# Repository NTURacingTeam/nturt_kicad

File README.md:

# NTU Racing Team KiCad Files

## Guide for configuring path variables and libraries

> [!NOTE]
> Before you start, please include the appropriate libraries and path variables to ensure components and their resources can be loaded correctly!

### 1. Configuring path variable

\

### 2. Configuring libraries
> [!NOTE]
> Configure symbol libraries and footprint libraries according to the README files located in each generation's directory. Images shown here are only for demonstration purposes only.

## Adding 3D models

1. Copy the .step/.wrl files to `EPx/Libraries/3d_models` folder
2. In the footprint editor (press Ctrl+E on a footprint in the PCB editor), open footprint properties, navigate to the 3D Models tab, and select the 3D model file with the folder icon to the left of the Show checkbox.
3. The path should be replaced with `${NTURT_KICAD_ROOT}/EPx/Libraries/3d_models/...`, if not, then you will need to set up the path variable.
4. Adjust the position of the model.
> [!NOTE]
> For a part that a 3D model would be helpful, if it is a part that came with KiCad, then consider "Save as" in the footprint editor to the project library, then edit the 3D model.\
> If it is already from a project library, remember to select "Open in library XXX" if it says "Editing XXX from board." on top. After you're done, right click the footprint in the PCB editor and select Update Footprint, check Update/reset 3D models.

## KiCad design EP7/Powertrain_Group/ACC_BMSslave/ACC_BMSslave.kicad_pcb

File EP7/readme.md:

# Libraries

## Path variable
Add `NTURT_KICAD_ROOT` to PATH environment variable, pointing to the git root of this repository.

## Symbols
Add the following symbol libraries with nickname:
  - `nturt_kicad_lib_EP7`:
```
${NTURT_KICAD_ROOT}/EP7/Libraries/nturt_kicad_lib_EP7.kicad_sym
```

## Footprints
Add the following footprint libraries with nickname:
  - `nturt_kicad_lib_EP7`:
```
${NTURT_KICAD_ROOT}/EP7/Libraries/nturt_kicad_lib_EP7.pretty
```

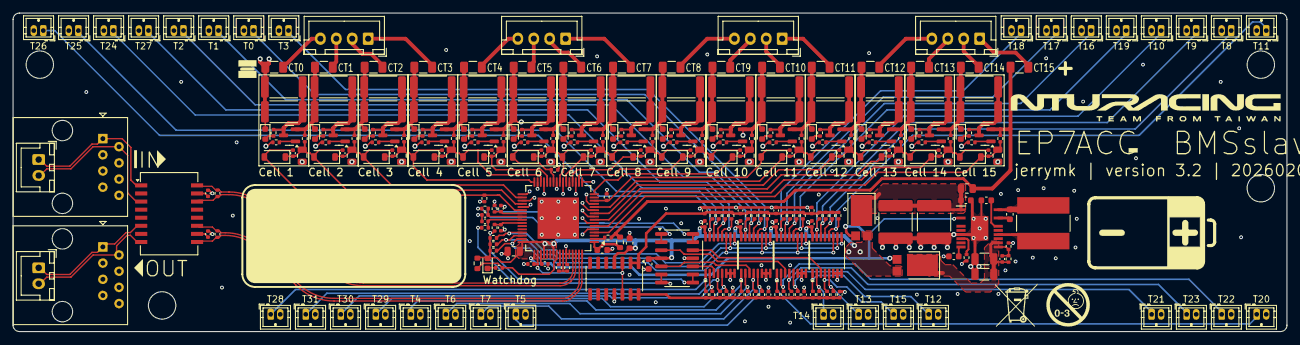
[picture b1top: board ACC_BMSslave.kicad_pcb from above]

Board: 4 copper layers, 200.0 x 50.0 mm, 310 parts (0 on the bottom side), 188 nets.

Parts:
C1, C2, C15: 100n; C_0603_1608Metric
C3, C57: 1u; C_0603_1608Metric
C4, C5, C6, C7: 10n; C_0402_1005Metric
C8, C9: 1u; C_0402_1005Metric
C10, C11: 100p; C_0402_1005Metric
C12: 1u; C_0805_2012Metric
C13, C63: 2.2u; C_2220_5750Metric
C14: 100p; C_0603_1608Metric
C16: 4.7p; C_0402_1005Metric
C17: 2.2u; C_0603_1608Metric
C18, C62: 22u; C_1206_3216Metric
C19, C20, C21, C22, C23, C24, C25, C26, C28, C30, C32, C34, C36, C38, C40, C42, C44, C46, C48, C50, C52, C54, C56, C58, C59, C60, C61: 100n; C_0402_1005Metric
C27, C29, C31, C33, C35, C37, C39, C41, C43, C45, C47, C49, C51, C53, C55: 100n 100V; C_0805_2012Metric
D1: BLUE; LED_0603_1608Metric
D2, D3, D4, D5, D6, D7, D8, D9, D10, D11, D12, D13, D14, D15, D16: RED; LED_0603_1608Metric
F1, F2, F3, F4, F5, F6, F7, F8, F9, F10, F11, F12, F13, F14, F15, F16: 0466.250NR; Fuse_1206_3216Metric
H1, H2, H3, H4: MountingHole; MountingHole_4.3mm_M4_ISO14580
IC1: ADBMS1818ASWAZ-R7; LQFP-64-1EP_10x10mm_P0.5mm_EP6.5x6.5mm
IC2: LT8631IFE#PBF; TSSOP-20 FE20(16) (EP Variation CB)
IC3, IC4, IC5, IC6, IC7, IC8, IC9, IC10, IC11, IC12, IC13, IC14, IC15, IC16, IC17: NX2301P,215; SOT-23
J1, J2, J3, J4: JST XH; JST_XH_B4B-XH-A_1x04_P2.50mm_Vertical
J5, J6, J7, J8, J9, J10, J11, J12, J13, J14, J15, J16, J17, J18, J19, J20, J21, J22, J23, J24, J25, J26, J27, J28, J29, J30, J31, J32, J33, J34, J35, J36: JST ZH; JST_ZH_B2B-ZR_1x02_P1.50mm_Vertical
J37, J38: RJ45; RJ45_Amphenol_54602-x08_Horizontal
J39: isoSPI_out; JST_XH_B2B-XH-A_1x02_P2.50mm_Vertical
J40: isoSPI_in; JST_XH_B2B-XH-A_1x02_P2.50mm_Vertical
L1: 22u/2A; L_Bourns-SRN8040_8x8.15mm
Q1, Q2: Q_NPN; D_PowerDI-5
R1: 100R; R_0805_2012Metric
R2: 100R; R_0603_1608Metric
R3, R4, R5, R6, R60, R65, R70, R75, R80, R85, R90, R95, R96, R101, R122, R123, R124, R125, R126: 10R; R_0402_1005Metric
R7, R8, R9, R10, R15, R16: 100R; R_0402_1005Metric
R11, R12, R13, R52, R56, R61, R66, R71, R76, R81, R86, R91, R97, R102, R106, R110, R114, R118: 1k; R_0402_1005Metric
R14: 1M; R_0603_1608Metric
R17: 24k; R_0402_1005Metric
R18: 1M/1%; R_0402_1005Metric
R19: 127k/1%; R_0402_1005Metric
R20, R21, R22, R23, R24, R25, R26, R27, R28, R29, R30, R31, R32, R33, R34, R35, R36, R37, R38, R39, R40, R41, R42, R43, R44, R45, R46, R47, R48, R49, R50, R51: 10k; R_0402_1005Metric
R53, R54, R57, R58, R62, R63, R67, R68, R72, R73, R77, R78, R82, R83, R87, R88, R92, R93, R98, R99, R103, R104, R107, R108, R111, R112, R115, R116, R119, R120: 51R; R_2512_6332Metric
R55, R59, R64, R69, R74, R79, R84, R89, R94, R100, R105, R109, R113, R117, R121: 3.3k; R_0402_1005Metric
R127, R128, R129: 47k; R_0402_1005Metric
TR1: Wuerth_749013011A; Transformer_Ethernet_Wuerth_749013011A
U1, U6: LM324DT; SO-14_3.9x8.65mm_P1.27mm
U2, U3, U4, U5: CD4051B; TSSOP-16_4.4x5mm_P0.65mm
Z1, Z2, Z3, Z4, Z5, Z6, Z7, Z8, Z9, Z10, Z11, Z12, Z13, Z14, Z15: MMSZ4692T1G; D_SOD-123

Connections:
/C0: C42.2, IC1.38 (C0), R6.2, Z8.2 (A)
/C1: C28.2, C41.1, C42.1, IC1.36 (C1), R95.2, Z1.2 (A), Z8.1 (K)
/C2: C27.1, C28.1, C30.2, IC1.34 (C2), R60.2, Z1.1 (K), Z2.2 (A)
/C3: C29.1, C30.1, C32.2, IC1.32 (C3), R65.2, Z2.1 (K), Z3.2 (A)
/C4: C31.1, C32.1, C34.2, IC1.30 (C4), R70.2, Z3.1 (K), Z4.2 (A)
/C5: C33.1, C34.1, IC1.28 (C5), R75.2, Z4.1 (K)
/C6: C36.2, IC1.26 (C6), R5.2, Z5.2 (A)
/C7: C35.1, C36.1, C38.2, IC1.24 (C7), R80.2, Z5.1 (K), Z6.2 (A)
/C8: C37.1, C38.1, C40.2, IC1.22 (C8), R85.2, Z6.1 (K), Z7.2 (A)
/C9: C39.1, C40.1, C44.2, IC1.20 (C9), R90.2, Z7.1 (K), Z9.2 (A)
/C10: C43.1, C44.1, C46.2, IC1.18 (C10), R96.2, Z9.1 (K), Z10.2 (A)
/C11: C45.1, C46.1, IC1.16 (C11), R101.2, Z10.1 (K)
/C12: C48.2, IC1.14 (C12), R4.2, Z11.2 (A)
/C13: C47.1, C48.1, C50.2, IC1.12 (C13), R122.2, Z11.1 (K), Z12.2 (A)
/C14: C49.1, C50.1, C52.2, IC1.10 (C14), R123.2, Z12.1 (K), Z13.2 (A)
/C15: C51.1, C52.1, C54.2, IC1.8 (C15), R124.2, Z13.1 (K), Z14.2 (A)
/C16: C53.1, C54.1, C56.2, IC1.6 (C16), R125.2, Z14.1 (K), Z15.2 (A)
/C17: C55.1, C56.1, IC1.4 (C17), R126.2, Z15.1 (K)
/C18: IC1.2 (C18), R3.2
/CT1: D2.1 (K), F2.2, IC4.2 (S), R53.1, R54.1, R95.1
/CT2: D4.1 (K), F3.2, IC3.2 (S), R60.1, R62.1, R63.1
/CT3: D5.1 (K), F4.2, IC5.2 (S), R65.1, R67.1, R68.1
/CT4: D6.1 (K), F5.2, IC6.2 (S), R70.1, R72.1, R73.1
/CT5: D7.1 (K), F6.2, IC7.2 (S), R5.1, R75.1, R77.1, R78.1
/CT6: D8.1 (K), F7.2, IC8.2 (S), R80.1, R82.1, R83.1
/CT7: D9.1 (K), F8.2, IC9.2 (S), R85.1, R87.1, R88.1
/CT8: D10.1 (K), F9.2, IC10.2 (S), R90.1, R92.1, R93.1
/CT9: D11.1 (K), F10.2, IC11.2 (S), R96.1, R98.1, R99.1
/CT10: D12.1 (K), F11.2, IC12.2 (S), R4.1, R101.1, R103.1, R104.1
/CT11: D13.1 (K), F12.2, IC13.2 (S), R107.1, R108.1, R122.1
/CT12: D14.1 (K), F13.2, IC14.2 (S), R111.1, R112.1, R123.1
/CT13: D15.1 (K), F14.2, IC15.2 (S), R115.1, R116.1, R124.1
/CT14: D16.1 (K), F15.2, IC16.2 (S), R119.1, R120.1, R125.1
/CT15: F16.2, IC17.2 (S), R1.1, R2.1, R3.1, R126.1
/DRIVE: IC1.49 (DRIVE), IC2.3 (EN/UV), Q1.B, Q2.B
/GPIO1: C4.1, IC1.39 (GPIO1), R7.2
/GPIO2: C5.1, IC1.40 (GPIO2), R8.2
/GPIO3: C7.1, IC1.41 (GPIO3), R10.2
/GPIO4: C6.1, IC1.42 (GPIO4), R9.2
/GPIO7: IC1.45 (GPIO7), R129.1, U2.9 (C), U3.9 (C), U4.9 (C), U5.9 (C)
/GPIO8: IC1.46 (GPIO8), R128.1, U2.10 (B), U3.10 (B), U4.10 (B), U5.10 (B)
/GPIO9: IC1.47 (GPIO9), R127.1, U2.11 (A), U3.11 (A), U4.11 (A), U5.11 (A)
/IN_N: IC1.61 (CSB), R16.1, TR1.16 (TX+)
/IN_P: IC1.62 (SCK), R16.2, TR1.14 (TX-)
/ISOSPI_IN+: J38.2, J40.2, TR1.3 (TD-)
/ISOSPI_IN-: J38.1, J40.1, TR1.1 (TD+)
/ISOSPI_OUT+: J37.2, J39.2, TR1.8 (RD-)
/ISOSPI_OUT-: J37.1, J39.1, TR1.6 (RD+)
/OUT_N: IC1.63 (IMB), R15.1, TR1.11 (RX+)
/OUT_P: IC1.64 (IPB), R15.2, TR1.9 (RX-)
/S1: IC1.37 (S1), R59.1
/S2: IC1.35 (S2), R55.1
/S3: IC1.33 (S3), R64.1
/S4: IC1.31 (S4), R69.1
/S5: IC1.29 (S5), R74.1
/S7: IC1.25 (S7), R79.1
/S8: IC1.23 (S8), R84.1
/S9: IC1.21 (S9), R89.1
/S10: IC1.19 (S10), R94.1
/S11: IC1.17 (S11), R100.1
/S13: IC1.13 (S13), R105.1
/S14: IC1.11 (S14), R109.1
/S15: IC1.9 (S15), R113.1
/S16: IC1.7 (S16), R117.1
/S17: IC1.5 (S17), R121.1
/T0: J5.1, R28.1, U3.13 (X0)
/T1: J13.1, R29.1, U3.14 (X1)
/T2: J21.1, R30.1, U3.15 (X2)
/T3: J29.1, R31.1, U3.12 (X3)
/T4: J6.1, R32.1, U3.1 (X4)
/T5: J14.1, R33.1, U3.5 (X5)
/T6: J22.1, R34.1, U3.2 (X6)
/T7: J30.1, R35.1, U3.4 (X7)
/T8: J7.1, R44.1, U5.13 (X0)
/T9: J15.1, R45.1, U5.14 (X1)
/T10: J23.1, R46.1, U5.15 (X2)
/T11: J31.1, R47.1, U5.12 (X3)
/T12: J8.1, R48.1, U5.1 (X4)
/T13: J16.1, R49.1, U5.5 (X5)
/T14: J24.1, R50.1, U5.2 (X6)
/T15: J32.1, R51.1, U5.4 (X7)
/T16: J9.1, R36.1, U4.13 (X0)
/T17: J17.1, R37.1, U4.14 (X1)
/T18: J25.1, R38.1, U4.15 (X2)
/T19: J33.1, R39.1, U4.12 (X3)
/T20: J10.1, R40.1, U4.1 (X4)
/T21: J18.1, R41.1, U4.5 (X5)
/T22: J26.1, R42.1, U4.2 (X6)
/T23: J34.1, R43.1, U4.4 (X7)
/T24: J11.1, R20.1, U2.13 (X0)
/T25: J19.1, R21.1, U2.14 (X1)
/T26: J27.1, R22.1, U2.15 (X2)
/T27: J35.1, R23.1, U2.12 (X3)
/T28: J12.1, R24.1, U2.1 (X4)
/T29: J20.1, R25.1, U2.5 (X5)
/T30: J28.1, R26.1, U2.2 (X6)
/T31: J36.1, R27.1, U2.4 (X7)
/VP: C2.1, IC1.1 (V+), R2.2
/VREF2: C9.1, IC1.50 (VREF2), U6.3 (+), U6.12 (+)
/power/VIN: C1.1, C13.1, C63.1, IC2.1 (VIN), Q2.C, R1.2
/tprobe_mux1/OUT: U1.10 (+), U2.3 (X)
/tprobe_mux1/VREF: C20.1, C22.1, C24.1, C26.1, R20.2, R21.2, R22.2, R23.2, R28.2, R29.2, R30.2, R31.2, R36.2, R37.2, R38.2, R39.2, R44.2, R45.2, R46.2, R47.2, U6.1, U6.2 (-)
/tprobe_mux1/VREF_b: C58.1, C59.1, C60.1, C61.1, R24.2, R25.2, R26.2, R27.2, R32.2, R33.2, R34.2, R35.2, R40.2, R41.2, R42.2, R43.2, R48.2, R49.2, R50.2, R51.2, U6.13 (-), U6.14
/tprobe_mux2/OUT: U1.5 (+), U3.3 (X)
/tprobe_mux3/OUT: U1.3 (+), U4.3 (X)
/tprobe_mux4/OUT: U1.12 (+), U5.3 (X)
Earth: C1.2, C2.2, C3.2, C4.2, C5.2, C6.2, C7.2, C8.2, C9.2, C10.2, C11.2, C12.2, C13.2, C14.2, C17.2, C18.2, C19.2, C20.2, C21.2, C22.2, C23.2, C24.2, C25.2, C26.2, C27.2, C29.2, C31.2, C33.2, C35.2, C37.2, C39.2, C41.2, C43.2, C45.2, C47.2, C49.2, C51.2, C53.2, C55.2, C57.2, C58.2, C59.2, C60.2, C61.2, C62.2, C63.2, D3.1 (K), F1.2, IC1.59 (V-_1), IC1.60 (V-_2), IC1.65 (V-_3), IC2.7 (SYNC/MODE), IC2.21 (GND), J5.2, J6.2, J7.2, J8.2, J9.2, J10.2, J11.2, J12.2, J13.2, J14.2, J15.2, J16.2, J17.2, J18.2, J19.2, J20.2, J21.2, J22.2, J23.2, J24.2, J25.2, J26.2, J27.2, J28.2, J29.2, J30.2, J31.2, J32.2, J33.2, J34.2, J35.2, J36.2, R6.1, R11.2, R17.2, R19.2, R57.1, R58.1, U1.11 (V-), U2.6 (INH), U2.7 (VEE), U2.8 (VSS), U3.6 (INH), U3.7 (VEE), U3.8 (VSS), U4.6 (INH), U4.7 (VEE), U4.8 (VSS), U5.6 (INH), U5.7 (VEE), U5.8 (VSS), U6.11 (V-)
unnamed: D1.1 (K), R13.1
unnamed: D2.2 (A), R52.2
unnamed: D3.2 (A), R56.2
unnamed: D4.2 (A), R61.2
unnamed: D5.2 (A), R66.2
unnamed: D6.2 (A), R71.2
unnamed: D7.2 (A), R76.2
unnamed: D8.2 (A), R81.2
unnamed: D9.2 (A), R86.2
unnamed: D10.2 (A), R91.2
unnamed: D11.2 (A), R97.2
unnamed: D12.2 (A), R102.2
unnamed: D13.2 (A), R106.2
unnamed: D14.2 (A), R110.2
unnamed: D15.2 (A), R114.2
unnamed: D16.2 (A), R118.2
unnamed: IC1.57 (IBIAS), R12.1
unnamed: IC1.58 (ICMP), R11.1, R12.2
unnamed: C8.1, IC1.51 (VREF1)
unnamed: IC1.56 (WDT), R13.2, R14.2
unnamed: C15.1, IC2.18 (BST)
unnamed: C16.1, IC2.11 (FB), R18.2, R19.1
unnamed: IC2.14 (IND), L1.1
unnamed: C17.1, IC2.16 (INTVCC)
unnamed: IC2.8 (RT), R17.1
unnamed: C15.2, IC2.20 (SW), L1.2
unnamed: C14.1, IC2.10 (TR/SS)
unnamed: C16.2, C18.1, C62.1, IC2.12 (VOUT), Q1.C, R18.1
unnamed: IC3.3 (D), R52.1, R53.2, R54.2
unnamed: IC3.1 (G), R55.2
unnamed: IC4.3 (D), R56.1, R57.2, R58.2
unnamed: IC4.1 (G), R59.2
unnamed: IC5.3 (D), R61.1, R62.2, R63.2
unnamed: IC5.1 (G), R64.2
unnamed: IC6.3 (D), R66.1, R67.2, R68.2
unnamed: IC6.1 (G), R69.2
unnamed: IC7.3 (D), R71.1, R72.2, R73.2
unnamed: IC7.1 (G), R74.2
unnamed: IC8.3 (D), R76.1, R77.2, R78.2
unnamed: IC8.1 (G), R79.2
unnamed: IC9.3 (D), R81.1, R82.2, R83.2
unnamed: IC9.1 (G), R84.2
unnamed: IC10.3 (D), R86.1, R87.2, R88.2
unnamed: IC10.1 (G), R89.2
unnamed: IC11.3 (D), R91.1, R92.2, R93.2
unnamed: IC11.1 (G), R94.2
unnamed: IC12.3 (D), R97.1, R98.2, R99.2
unnamed: IC12.1 (G), R100.2
unnamed: IC13.3 (D), R102.1, R103.2, R104.2
unnamed: IC13.1 (G), R105.2
unnamed: IC14.3 (D), R106.1, R107.2, R108.2
unnamed: IC14.1 (G), R109.2
unnamed: IC15.3 (D), R110.1, R111.2, R112.2
unnamed: IC15.1 (G), R113.2
unnamed: IC16.3 (D), R114.1, R115.2, R116.2
unnamed: IC16.1 (G), R117.2
unnamed: IC17.3 (D), R118.1, R119.2, R120.2
unnamed: IC17.1 (G), R121.2
unnamed: F4.1, J1.1
unnamed: F3.1, J1.2
unnamed: F2.1, J1.3
unnamed: F1.1, J1.4
unnamed: F8.1, J2.1
unnamed: F7.1, J2.2
unnamed: F6.1, J2.3
unnamed: F5.1, J2.4
unnamed: F12.1, J3.1
unnamed: F11.1, J3.2
unnamed: F10.1, J3.3
unnamed: F9.1, J3.4
unnamed: F16.1, J4.1
unnamed: F15.1, J4.2
unnamed: F14.1, J4.3
unnamed: F13.1, J4.4
unnamed: C10.1, TR1.10 (C_RX)
unnamed: C11.1, TR1.15 (C_TX)
unnamed: R8.1, U1.1, U1.2 (-)
unnamed: R10.1, U1.6 (-), U1.7
unnamed: R9.1, U1.8, U1.9 (-)
unnamed: R7.1, U1.13 (-), U1.14
VREG: C3.1, C12.1, C19.1, C21.1, C23.1, C25.1, C57.1, D1.2 (A), IC1.48 (VREG), IC1.52 (DTEN), IC1.55 (ISOMD), Q1.E, Q2.E, R14.1, R127.2, R128.2, R129.2, U1.4 (V+), U2.16 (VDD), U3.16 (VDD), U4.16 (VDD), U5.16 (VDD), U6.4 (V+)

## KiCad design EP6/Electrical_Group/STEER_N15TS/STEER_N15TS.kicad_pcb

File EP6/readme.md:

# Libraries

## Path variable
Add `NTURT_KICAD_ROOT` to PATH environment variable, pointing to the git root of this repository.

## Symbols
Add the following symbol libraries with nickname:
  - `nturt_kicad_lib_EP6`:
```
${NTURT_KICAD_ROOT}/EP6/Project_Library_EP6/nturt_kicad_lib.kicad_sym
```
  - `SamacSys_Parts_EP6`:
```
${NTURT_KICAD_ROOT}/EP6/Project_Library_EP6/SamacSys_Parts.kicad_sym
```

## Footprints
Add the following footprint libraries with nickname:
  - `nturt_kicad_lib_EP6`:
```
${NTURT_KICAD_ROOT}/EP6/Project_Library_EP6/nturt_kicad_lib.pretty
```
  - `SamacSys_Parts_EP6`:
```
${NTURT_KICAD_ROOT}/EP6/Project_Library_EP6/SamacSys_Parts.pretty
```

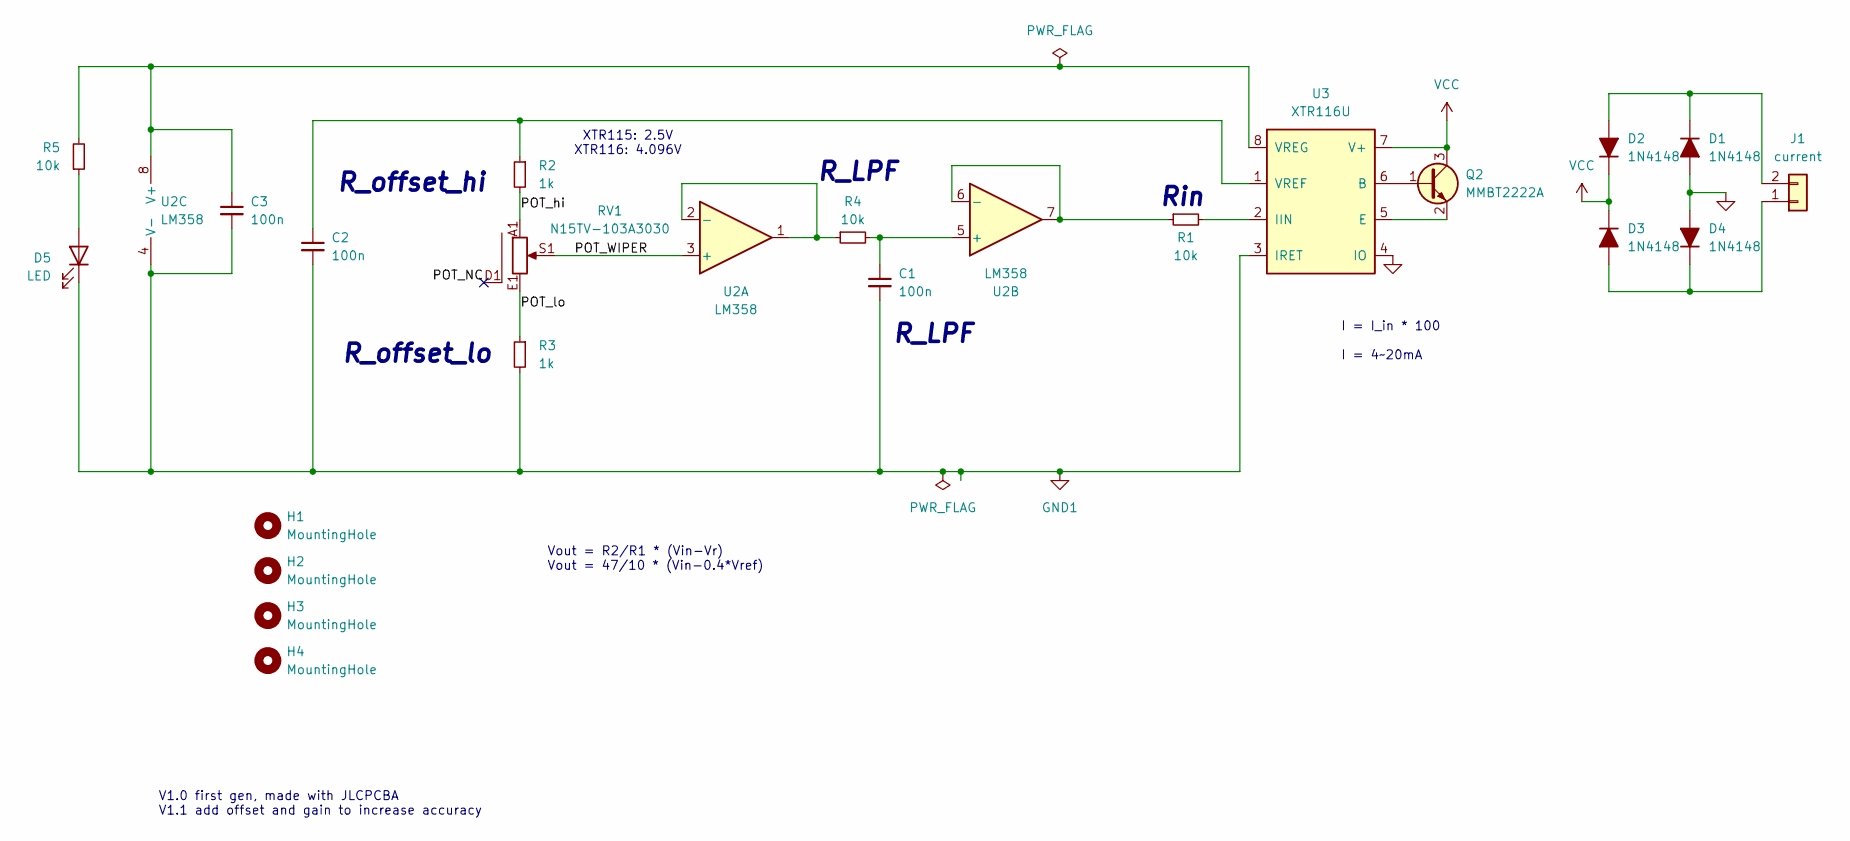
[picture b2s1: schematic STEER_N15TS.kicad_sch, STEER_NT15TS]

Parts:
C1, C2, C3: 100n; C_0603_1608Metric
D1, D2, D3, D4: 1N4148; D_SOD-323_HandSoldering
D5: LED; LED_0603_1608Metric
H1, H2, H3, H4: MountingHole; MountingHole_3.2mm_M3
J1: current; JST_XH_S2B-XH-A_1x02_P2.50mm_Horizontal; Part Number 1-0201FBV0T
Q2: MMBT2222A; SOT-23
R1, R4, R5: 10k; R_0603_1608Metric
R2, R3: 1k; R_0603_1608Metric
RV1: N15TV-103A3030; N15TS103A3030
U2: LM358; SOIC-8_3.9x4.9mm_P1.27mm
U3: XTR116U; SOIC-8_3.9x4.9mm_P1.27mm

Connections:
/POT_NC: RV1.D1 (DUMMY)
/POT_WIPER: RV1.S1 (WIPER), U2.3 (+)
/POT_hi: R2.2, RV1.A1 (INITIAL)
/POT_lo: R3.1, RV1.E1 (FINAL)
GND: D1.2 (A), D4.2 (A), U3.4 (IO)
GND1: C1.2, C2.2, C3.2, D5.1 (K), R3.2, U2.4 (V-), U3.3 (IRET)
unnamed: D1.1 (K), D2.2 (A), J1.2
unnamed: D3.2 (A), D4.1 (K), J1.1
unnamed: D5.2 (A), R5.1
unnamed: Q2.1 (B), U3.6 (B)
unnamed: Q2.2 (E), U3.5 (E)
unnamed: R4.1, U2.1, U2.2 (-)
unnamed: C1.1, R4.2, U2.5 (+)
unnamed: R1.1, U2.6 (-), U2.7
unnamed: C3.1, R5.2, U2.8 (V+), U3.8 (VREG)
unnamed: R1.2, U3.2 (IIN)
unnamed: C2.1, R2.1, U3.1 (VREF)
VCC: D2.1 (K), D3.1 (K), Q2.3 (C), U3.7 (V+)

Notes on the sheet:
R_offset_lo
Vout = R2/R1 * (Vin-Vr) Vout = 47/10 * (Vin-0.4*Vref)
R_offset_hi
I = I_in * 100 I = 4~20mA
R_LPF
XTR115: 2.5V XTR116: 4.096V
V1.0 first gen, made with JLCPCBA V1.1 add offset and gain to increase accuracy
Rin

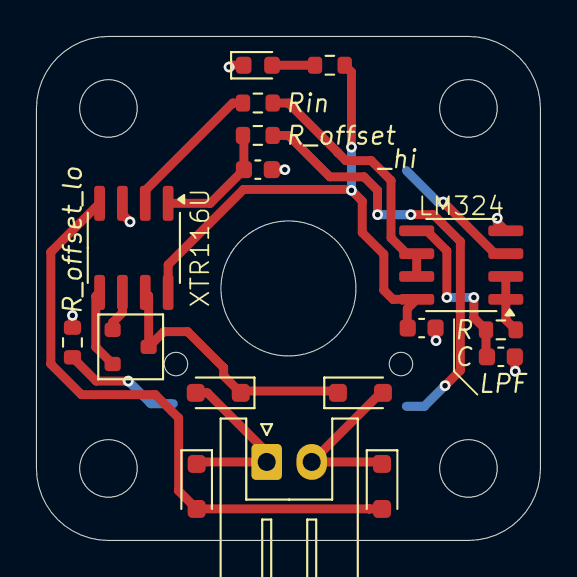
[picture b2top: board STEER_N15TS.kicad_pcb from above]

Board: 2 copper layers, 28.0 x 28.0 mm, 22 parts (1 on the bottom side), 17 nets.

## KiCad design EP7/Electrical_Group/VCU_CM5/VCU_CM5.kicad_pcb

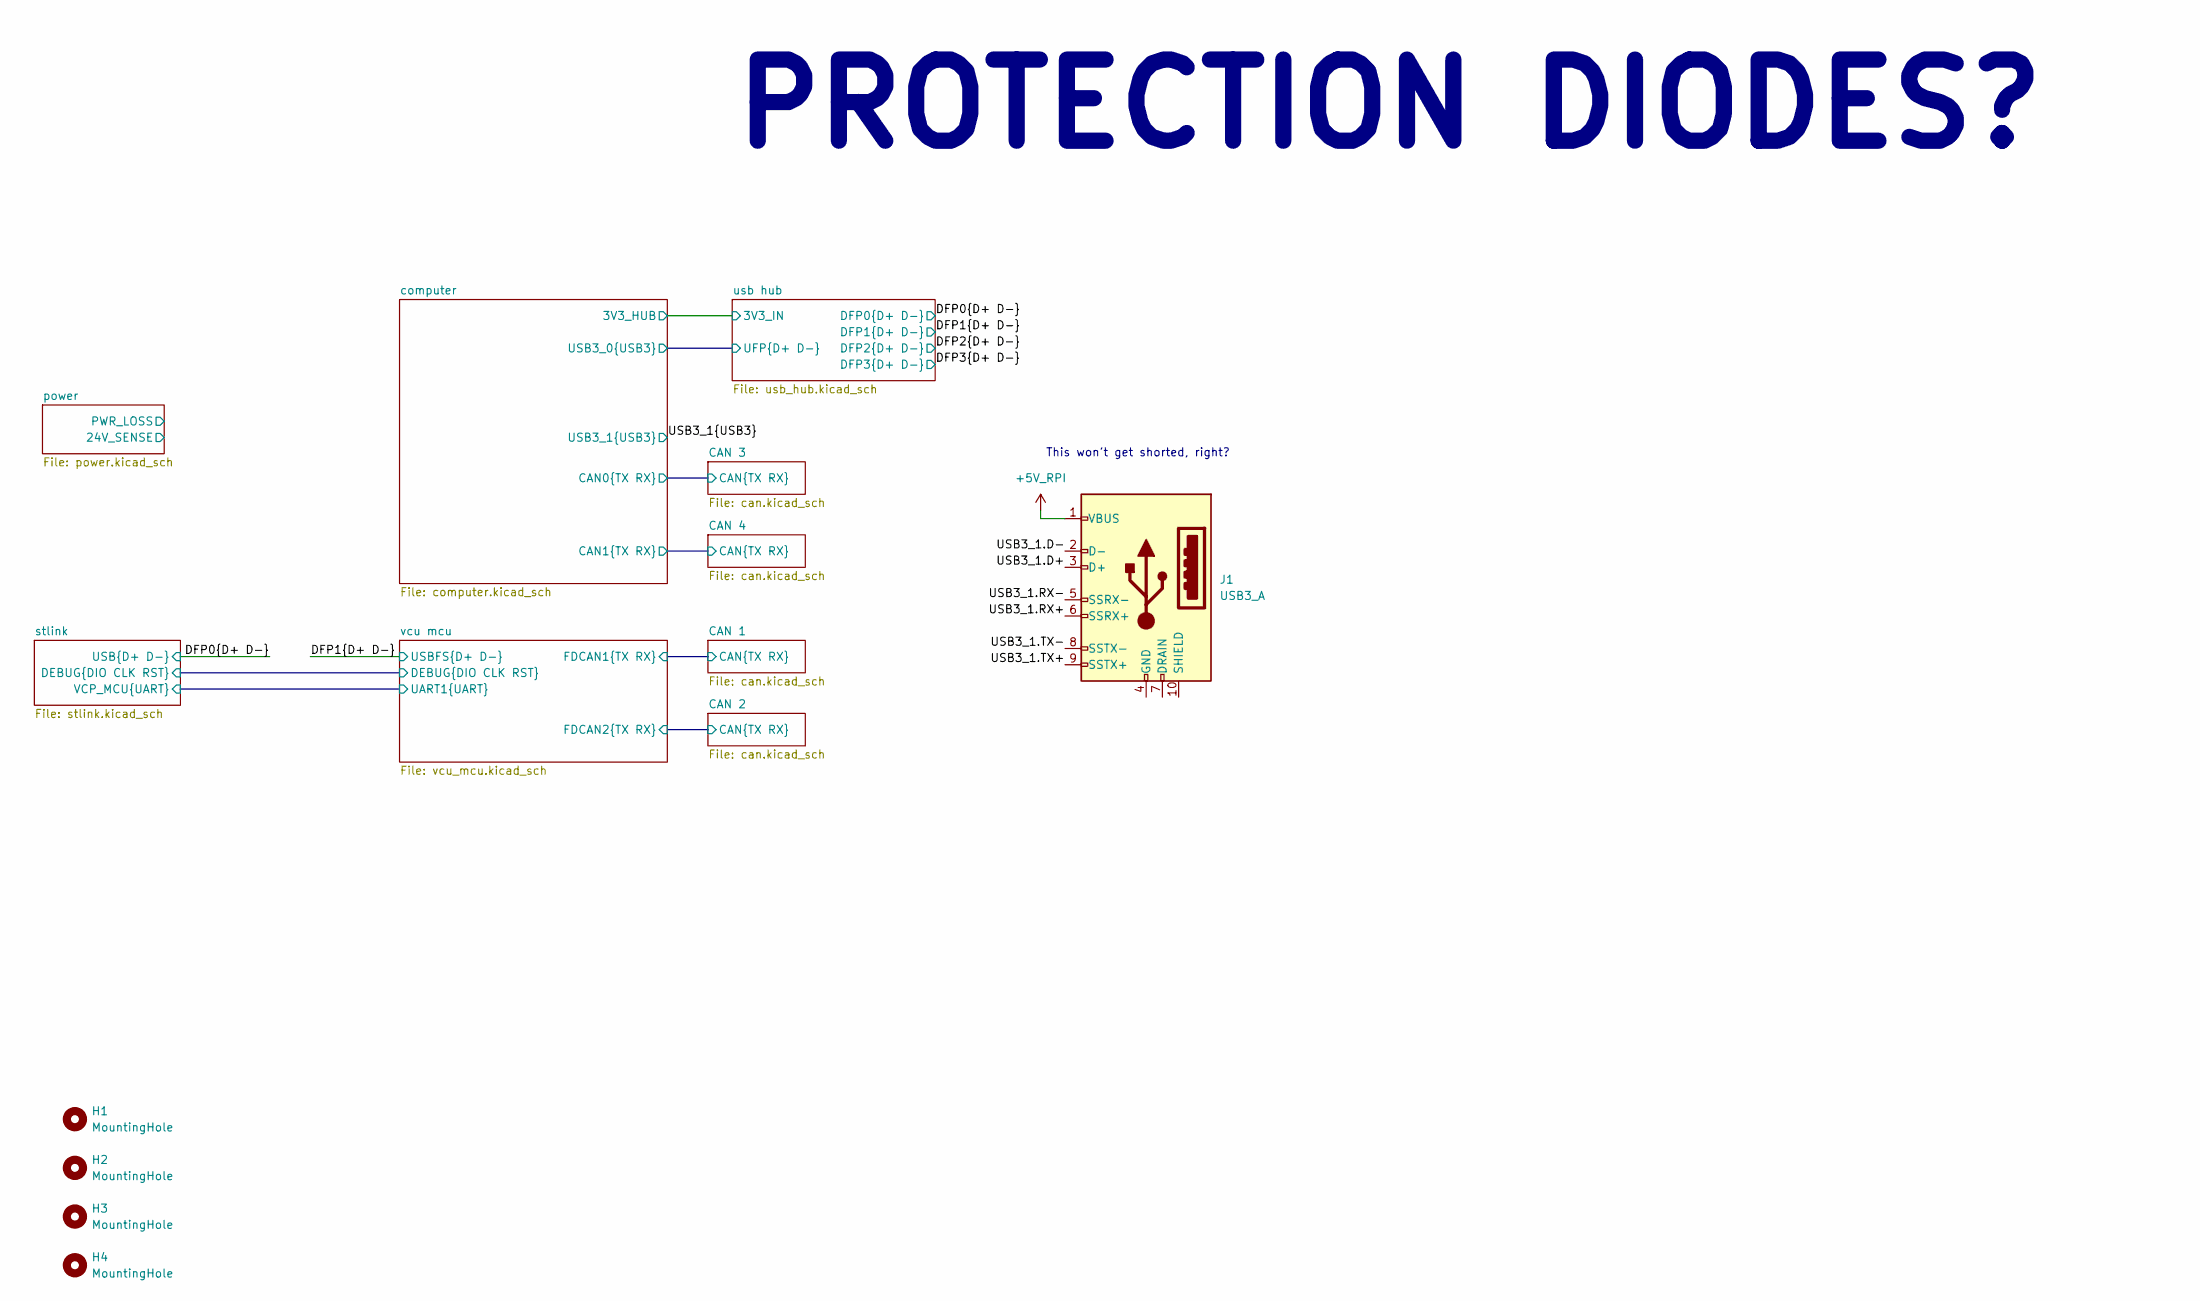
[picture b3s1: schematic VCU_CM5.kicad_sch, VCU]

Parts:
H1, H2, H3, H4: MountingHole; MountingHole_3.2mm_M3
J1: USB3_A; USB3_A_Molex_48393-001

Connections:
+5V_RPI: J1.1 (VBUS); also elsewhere on the board
/USB3_1.D+: J1.3 (D+); also elsewhere on the board
/USB3_1.D-: J1.2 (D-); also elsewhere on the board
/USB3_1.RX+: J1.6 (SSRX+); also elsewhere on the board
/USB3_1.RX-: J1.5 (SSRX-); also elsewhere on the board
/USB3_1.TX+: J1.9 (SSTX+); also elsewhere on the board
/USB3_1.TX-: J1.8 (SSTX-); also elsewhere on the board

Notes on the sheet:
PROTECTION DIODES?
This won't get shorted, right?

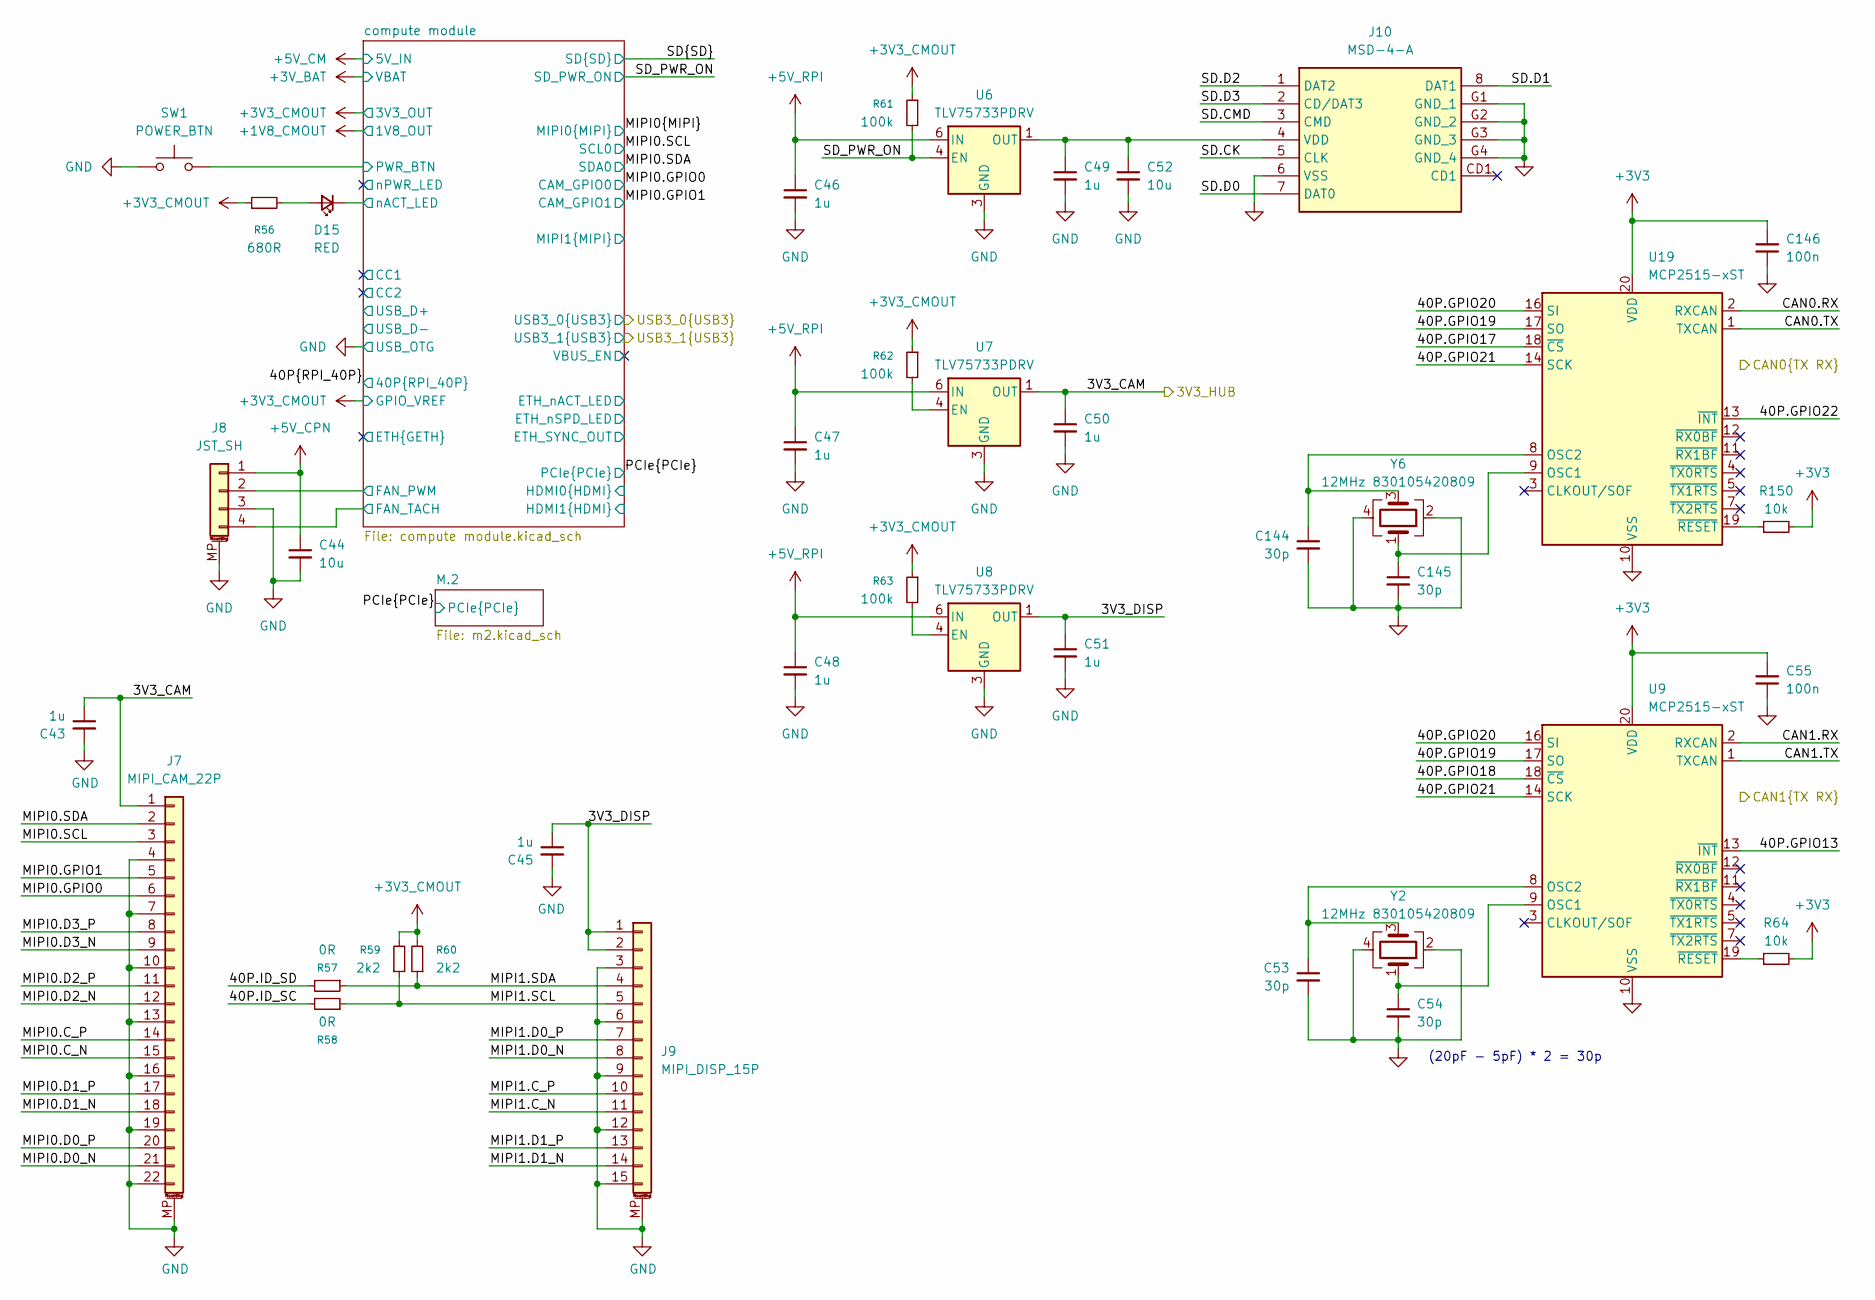
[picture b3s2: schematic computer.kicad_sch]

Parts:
C43, C45, C46, C47, C48, C49, C50, C51: 1u; C_0402_1005Metric
C44, C52: 10u; C_0603_1608Metric
C53, C54, C144, C145: 30p; C_0402_1005Metric
C55, C146: 100n; C_0402_1005Metric
D15: RED; LED_0603_1608Metric
J7: MIPI_CAM_22P; Amphenol_SFV22R-2STE1HLF_1x22-1MP_P0.50mm_Horizontal_TopCon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; Part Description 22 Position FFC, FPC Connector Contacts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
J8: JST_SH; JST_SH_BM04B-SRSS-TB_1x04-1MP_P1.00mm_Vertical; Part Description 4 pin vertical 1mm pitch connector
J9: MIPI_DISP_15P; Molex_200528-0150_1x15-1MP_P1.00mm_Horizontal
J10: MSD-4-A; MSD4A; Mouser Part Number 179-MSD-4-A
R56: 680R; R_0402_1005Metric
R57, R58: 0R; R_0402_1005Metric
R59, R60: 2k2; R_0402_1005Metric
R61, R62, R63: 100k; R_0402_1005Metric
R64, R150: 10k; R_0402_1005Metric
SW1: POWER_BTN; SW_SPST_PTS810
U6, U7, U8: TLV75733PDRV; WSON-6-1EP_2x2mm_P0.65mm_EP1x1.6mm
U9, U19: MCP2515-xST; TSSOP-20_4.4x6.5mm_P0.65mm
Y2, Y6: 12MHz 830105420809; Crystal_SMD_3225-4Pin_3.2x2.5mm

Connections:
+3V3: C55.2, C146.2, R64.2, R150.2, U9.20 (VDD), U19.20 (VDD); also elsewhere on the board
+3V3_CMOUT: R56.1, R59.2, R60.2, R61.1, R62.1, R63.1; also elsewhere on the board
+5V_CPN: C44.1, J8.1
+5V_RPI: C46.1, C47.1, C48.1, U6.6 (IN), U7.6 (IN), U8.6 (IN); also elsewhere on the board
/CAN 3/CAN.RX: U19.2 (RXCAN); also elsewhere on the board
/CAN 3/CAN.TX: U19.1 (TXCAN); also elsewhere on the board
/CAN 4/CAN.RX: U9.2 (RXCAN); also elsewhere on the board
/CAN 4/CAN.TX: U9.1 (TXCAN); also elsewhere on the board
/computer/3V3_CAM: C43.1, C50.1, J7.1, U7.1 (OUT); also elsewhere on the board
/computer/3V3_DISP: C45.1, C51.1, J9.1, J9.2, U8.1 (OUT)
/computer/40P.GPIO13: U9.13 (~INT); also elsewhere on the board
/computer/40P.GPIO17: U19.18 (~CS); also elsewhere on the board
/computer/40P.GPIO18: U9.18 (~CS); also elsewhere on the board
/computer/40P.GPIO19: U9.17 (SO), U19.17 (SO); also elsewhere on the board
/computer/40P.GPIO20: U9.16 (SI), U19.16 (SI); also elsewhere on the board
/computer/40P.GPIO21: U9.14 (SCK), U19.14 (SCK); also elsewhere on the board
/computer/40P.GPIO22: U19.13 (~INT); also elsewhere on the board
/computer/40P.ID_SC: R58.2; also elsewhere on the board
/computer/40P.ID_SD: R57.2; also elsewhere on the board
/computer/MIPI0.C_N: J7.15; also elsewhere on the board
/computer/MIPI0.C_P: J7.14; also elsewhere on the board
/computer/MIPI0.D0_N: J7.21; also elsewhere on the board
/computer/MIPI0.D0_P: J7.20; also elsewhere on the board
/computer/MIPI0.D1_N: J7.18; also elsewhere on the board
/computer/MIPI0.D1_P: J7.17; also elsewhere on the board
/computer/MIPI0.D2_N: J7.12; also elsewhere on the board
/computer/MIPI0.D2_P: J7.11; also elsewhere on the board
/computer/MIPI0.D3_N: J7.9; also elsewhere on the board
/computer/MIPI0.D3_P: J7.8; also elsewhere on the board
/computer/MIPI0.GPIO0: J7.6; also elsewhere on the board
/computer/MIPI0.GPIO1: J7.5; also elsewhere on the board
/computer/MIPI0.SCL: J7.3; also elsewhere on the board
/computer/MIPI0.SDA: J7.2; also elsewhere on the board
/computer/MIPI1.SCL: J9.5, R58.1, R59.1
/computer/MIPI1.SDA: J9.4, R57.1, R60.1
/computer/SD.CK: J10.5 (CLK); also elsewhere on the board
/computer/SD.CMD: J10.3 (CMD); also elsewhere on the board
/computer/SD.D0: J10.7 (DAT0); also elsewhere on the board
/computer/SD.D1: J10.8 (DAT1); also elsewhere on the board
/computer/SD.D2: J10.1 (DAT2); also elsewhere on the board
/computer/SD.D3: J10.2 (CD/DAT3); also elsewhere on the board
/computer/SD_PWR_ON: R61.2, U6.4 (EN); also elsewhere on the board
/computer/compute module/FAN_PWM: J8.2; also elsewhere on the board
/computer/compute module/FAN_TACH: J8.4; also elsewhere on the board
/computer/compute module/MIPI1.C_N: J9.11; also elsewhere on the board
/computer/compute module/MIPI1.C_P: J9.10; also elsewhere on the board
/computer/compute module/MIPI1.D0_N: J9.8; also elsewhere on the board
/computer/compute module/MIPI1.D0_P: J9.7; also elsewhere on the board
/computer/compute module/MIPI1.D1_N: J9.14; also elsewhere on the board
/computer/compute module/MIPI1.D1_P: J9.13; also elsewhere on the board
/computer/compute module/PWR_BTN: SW1.2; also elsewhere on the board
/computer/compute module/nACT_LED: D15.1 (K); also elsewhere on the board
GND: C43.2, C44.2, C45.2, C46.2, C47.2, C48.2, C49.2, C50.2, C51.2, C52.2, C53.2, C54.2, C55.1, C144.2, C145.2, C146.1, J7.4, J7.7, J7.10, J7.13, J7.16, J7.19, J7.22, J7.MP (MountPin), J8.3, J8.MP (MountPin), J9.3, J9.6, J9.9, J9.12, J9.15, J9.MP (MountPin), J10.6 (VSS), J10.G1 (GND_1), J10.G2 (GND_2), J10.G3 (GND_3), J10.G4 (GND_4), SW1.1, U6.3 (GND), U6.7 (GND), U7.3 (GND), U7.7 (GND), U8.3 (GND), U8.7 (GND), U9.10 (VSS), U19.10 (VSS), Y2.2, Y2.4, Y6.2, Y6.4; also elsewhere on the board
unnamed: D15.2 (A), R56.2
unnamed: C49.1, C52.1, J10.4 (VDD), U6.1 (OUT)
unnamed: R62.2, U7.4 (EN)
unnamed: R63.2, U8.4 (EN)
unnamed: C54.1, U9.9 (OSC1), Y2.1
unnamed: C53.1, U9.8 (OSC2), Y2.3
unnamed: R64.1, U9.19 (~RESET)
unnamed: C145.1, U19.9 (OSC1), Y6.1
unnamed: C144.1, U19.8 (OSC2), Y6.3
unnamed: R150.1, U19.19 (~RESET)

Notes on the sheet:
(20pF - 5pF) * 2 = 30p
